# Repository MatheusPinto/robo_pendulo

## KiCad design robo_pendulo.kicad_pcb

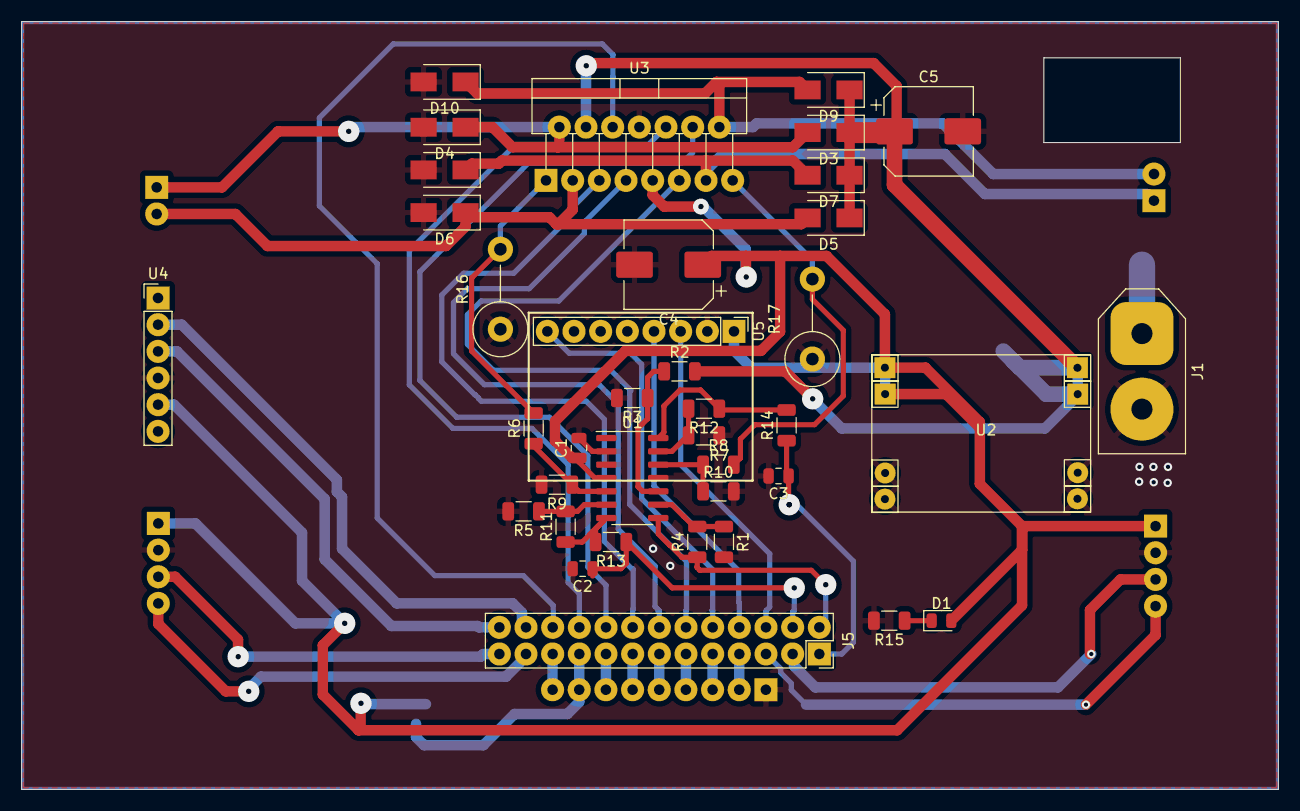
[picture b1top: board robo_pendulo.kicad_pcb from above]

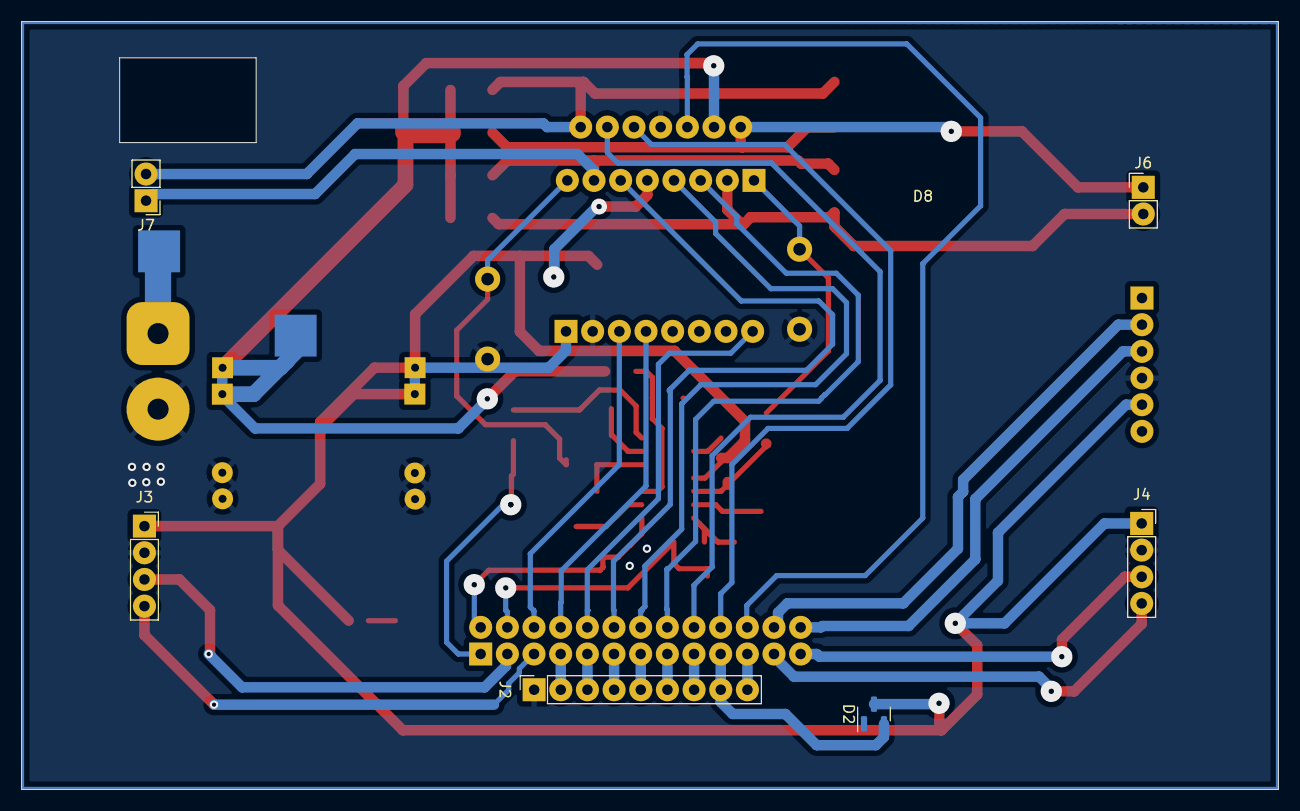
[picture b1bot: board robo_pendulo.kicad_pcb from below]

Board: 2 copper layers, 119.7 x 73.2 mm, 44 parts (6 on the bottom side), 44 nets.

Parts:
C1: 100n; C_0805_2012Metric
C2, C3: 1u; C_0805_2012Metric
C4, C5: 100n; CP_Elec_8x10
D1: LED; LED_0805_2012Metric
D2: D_Schottky; SOT-23
D3, D4, D5, D6, D7, D8, D9, D10: 1N4007; D_SMA
J1: Conn_01x02; AMASS_XT60-M_1x02_P7.20mm_Vertical
J2: Conn_01x09; PinSocket_1x09_P2.54mm_Vertical
J3, J4: Conn_01x04; PinSocket_1x04_P2.54mm_Vertical
J5: Conn_02x13_Odd_Even; PinSocket_2x13_P2.54mm_Vertical
J6, J7: Conn_01x02; PinHeader_1x02_P2.54mm_Vertical
R1, R2: 33k; R_1206_3216Metric
R3, R4, R10, R12: 10k; R_1206_3216Metric
R5, R6: 3k; R_1206_3216Metric
R7, R8: 1k; R_1206_3216Metric
R9, R11: 47k; R_1206_3216Metric
R13, R14: 150; R_1206_3216Metric
R15: 1K; R_1206_3216Metric
R16, R17: 0.1; R_Axial_DIN0516_L15.5mm_D5.0mm_P7.62mm_Vertical
U1: LM324; SOIC-14_3.9x8.7mm_P1.27mm
U2: mini-DC-DC
U3: L298HN; TO-220-15_P2.54x2.54mm_StaggerOdd_Lead4.58mm_Vertical
U4: HC-05; PinHeader_1x06_P2.54mm_Vertical
U5: MPU-6050; PinHeader_1x08_P2.54mm_Vertical

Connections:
5V_OUT: D2.2 (K), J2.8, J5.19
+5V: C1.1, C4.1, D1.2 (A), D2.3 (A), J3.1, J4.1, U1.4 (V+), U2.1 (OUT+), U2.2 (OUT+), U3.9 (Vss), U4.5 (Vcc), U5.1 (VCC)
+BATT: C5.1, D3.1 (K), D5.1 (K), D7.1 (K), D9.1 (K), R2.2, U2.5 (IN+), U2.6 (IN+), U3.4 (Vs)
/CURR_LM: R6.2, R16.2, U3.1 (SENSE_A)
/CURR_RM: R8.2, R17.2, U3.15 (SENSE_B)
CLP: J2.9, J5.21
ENC0_A: J3.3, J5.3
ENC0_B: J3.4, J5.5
ENC1_A: J4.3, J5.25
ENC1_B: J4.4, J5.23
GND: C1.2, C2.2, C3.2, C4.2, C5.2, D4.2 (A), D6.2 (A), D8.2 (A), D10.2 (A), J1.2, J2.1, J3.2, J4.2, R1.2, R3.2, R5.2, R7.2, R9.2, R10.2, R15.2, R16.1, R17.1, U1.2 (-), U1.3 (+), U1.11 (V-), U2.3 (OUT-), U2.4 (OUT-), U2.7 (IN-), U2.8 (IN-), U3.8 (GND), U4.4 (GND), U5.2 (GND)
IMU_INT: J5.10, U5.8 (INT)
IMU_SCL: J5.6, U5.3 (SCL)
IMU_SDA: J5.8, U5.4 (SDA)
MEAS_BATT: J5.2, R4.1, U1.8
MEAS_LM: C2.1, J5.4, R13.1
MEAS_RM: C3.1, J5.1, R14.1
MOT_ENA: J5.22, U3.6 (EnA)
MOT_ENB: J5.12, U3.11 (EnB)
MOT_IN1: J5.16, U3.5 (IN1)
MOT_IN2: J5.14, U3.7 (IN2)
MOT_IN3: J5.20, U3.10 (IN3)
MOT_IN4: J5.18, U3.12 (IN4)
MOT_OUT1: D3.2 (A), D4.1 (K), J6.1, U3.2 (OUT1)
MOT_OUT2: D5.2 (A), D6.1 (K), J6.2, U3.3 (OUT2)
MOT_OUT3: D7.2 (A), D8.1 (K), J7.1, U3.13 (OUT3)
MOT_OUT4: D9.2 (A), D10.1 (K), J7.2, U3.14 (OUT4)
NEAR: J2.2, J5.7
unnamed: D1.1 (K), R15.1
unnamed: R1.1, R4.2, U1.9 (-)
unnamed: R2.1, R3.1, U1.10 (+)
unnamed: R6.1, R9.1, U1.5 (+)
unnamed: R8.1, R10.1, U1.12 (+)
unnamed: R11.1, R13.2, U1.7
unnamed: R5.1, R11.2, U1.6 (-)
unnamed: R12.1, R14.2, U1.14
unnamed: R7.1, R12.2, U1.13 (-)
RXB: J5.24, U4.2 (Rxd)
SS1: J2.7, J5.17
SS2: J2.6, J5.15
SS3: J2.5, J5.13
SS4: J2.4, J5.11
SS5: J2.3, J5.9
TXB: J5.26, U4.3 (Txd)

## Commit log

2022-12-13 começo do desenvolvimento do leiaute
2026-04-17 Adjust board layout
